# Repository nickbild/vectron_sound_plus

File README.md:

# Vectron Sound Plus

Vectron Sound Plus uses the General Instrument AY-3-8910 sound generator to produce 8-bit retro audio.

## How It Works

The simple design exposes the AY-3-8910's data bus and control pins so that an external system can control it.  The required crystal oscillator and audio output circuitry are also included so that any speaker can be connected via a TRS cable through the onboard jack.

This is the circuit design:

## Media

Here, the Vectron Sound Plus is being controlled by the [Vectron 65 Plus computer](https://github.com/nickbild/vectron_65_plus):

You can download an [MP3 here](https://github.com/nickbild/vectron_sound_plus/blob/main/media/vectron_65_audio.mp3?raw=true) of a tune I made with it.

Vectron Sound Plus can also be controlled via a Raspberry Pi using [my Python library](https://github.com/nickbild/ay-3-8910).

## Bill of Materials

- 1 x General Instrument AY-3-8910 sound generator
- 1 x 2 MHz crystal oscillator
- 1 x 220 uF electrolytic capacitor
- 1 x 47 uF electrolytic capacitor
- 1 x 1K resistor
- 2 x 0.1 uF ceramic capacitors
- 1 x TRS jack connector
- 1 x PCB ([Kicad design files](https://github.com/nickbild/vectron_sound_plus/tree/main/vectron_sound_kicad))

## About the Author

[Nick A. Bild, MS](https://nickbild79.firebaseapp.com/#!/)

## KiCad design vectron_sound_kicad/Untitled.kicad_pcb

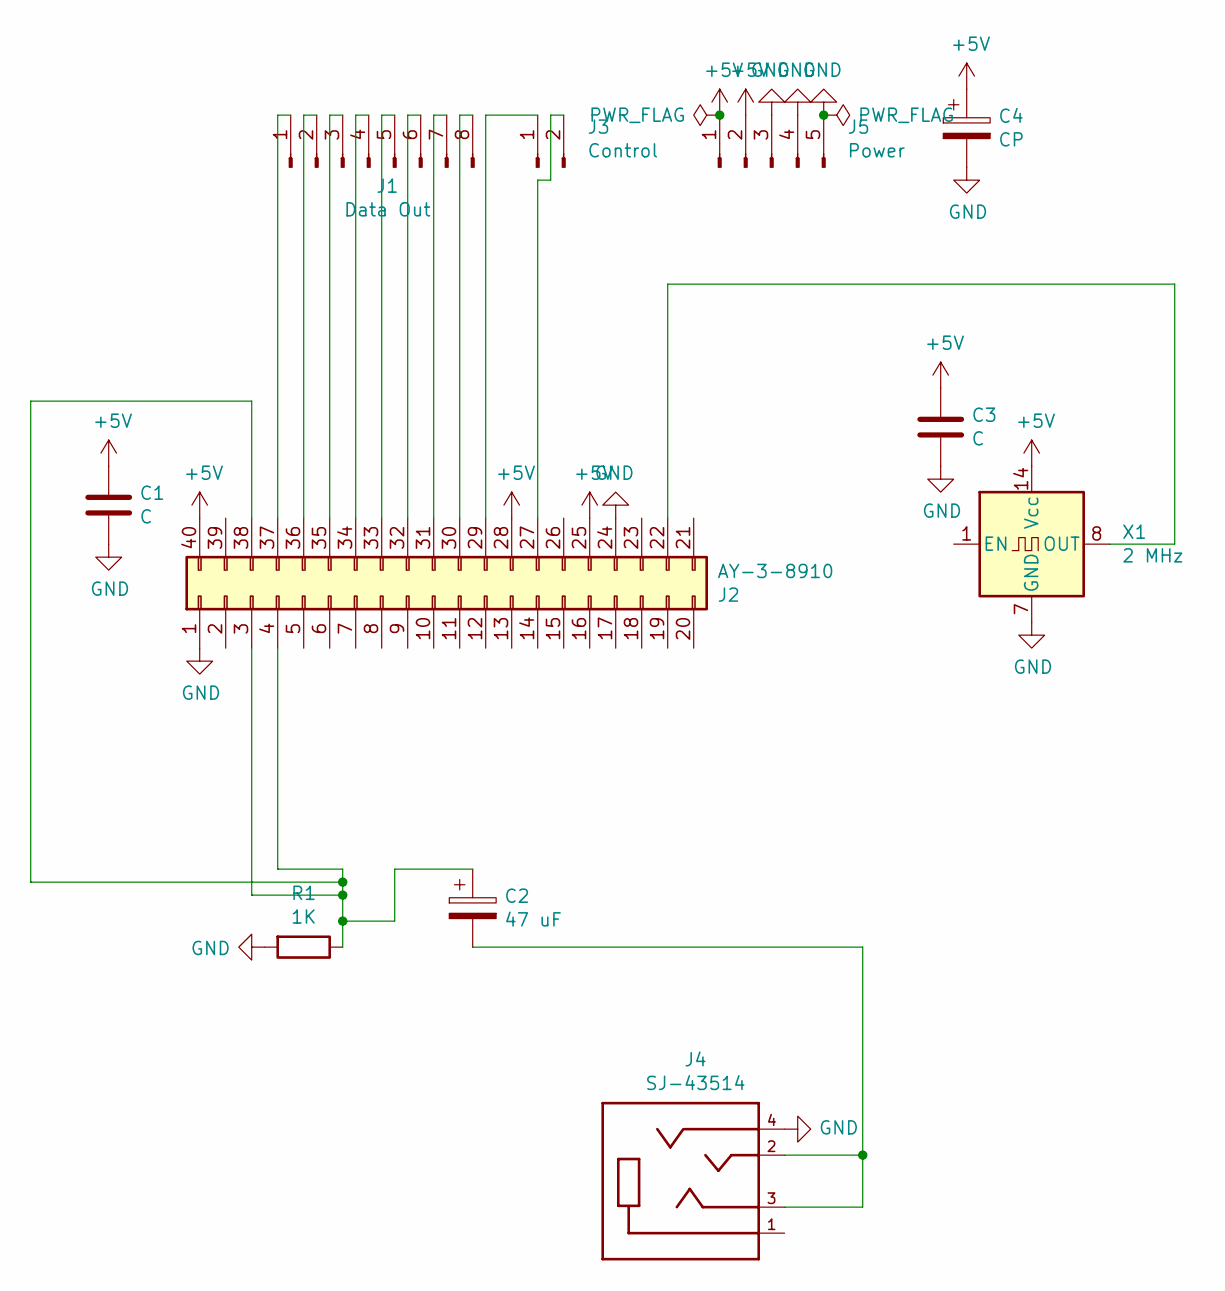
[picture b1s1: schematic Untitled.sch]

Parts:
C1, C3: C; C_Disc_D3.0mm_W2.0mm_P2.50mm
C2: 47 uF; CP_Radial_D4.0mm_P2.00mm
C4: CP; CP_Radial_D5.0mm_P2.50mm
J1: Data Out; PinHeader_1x08_P2.54mm_Vertical
J2: AY-3-8910; DIP-40_W15.24mm
J3: Control; PinHeader_1x02_P2.54mm_Vertical
J4: SJ-43514; CUI_SJ-43514; PART_REV 1.04
J5: Power; PinHeader_1x05_P2.54mm_Vertical
R1: 1K; R_Axial_DIN0204_L3.6mm_D1.6mm_P5.08mm_Horizontal
X1: 2 MHz; Oscillator_DIP-14

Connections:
+5V: C1.1, C3.1, C4.1, J2.25, J2.28, J2.40, J5.1, J5.2, X1.14 (Vcc)
GND: C1.2, C3.2, C4.2, J2.1, J2.24, J4.4, J5.3, J5.4, J5.5, R1.2, X1.7 (GND)
unnamed: C2.1, J2.3, J2.4, J2.38, R1.1
unnamed: C2.2, J4.2, J4.3
unnamed: J1.1, J2.37
unnamed: J1.2, J2.36
unnamed: J1.3, J2.35
unnamed: J1.4, J2.34
unnamed: J1.5, J2.33
unnamed: J1.6, J2.32
unnamed: J1.7, J2.31
unnamed: J1.8, J2.30
unnamed: J2.22, X1.8 (OUT)
unnamed: J2.27, J3.2
unnamed: J2.29, J3.1

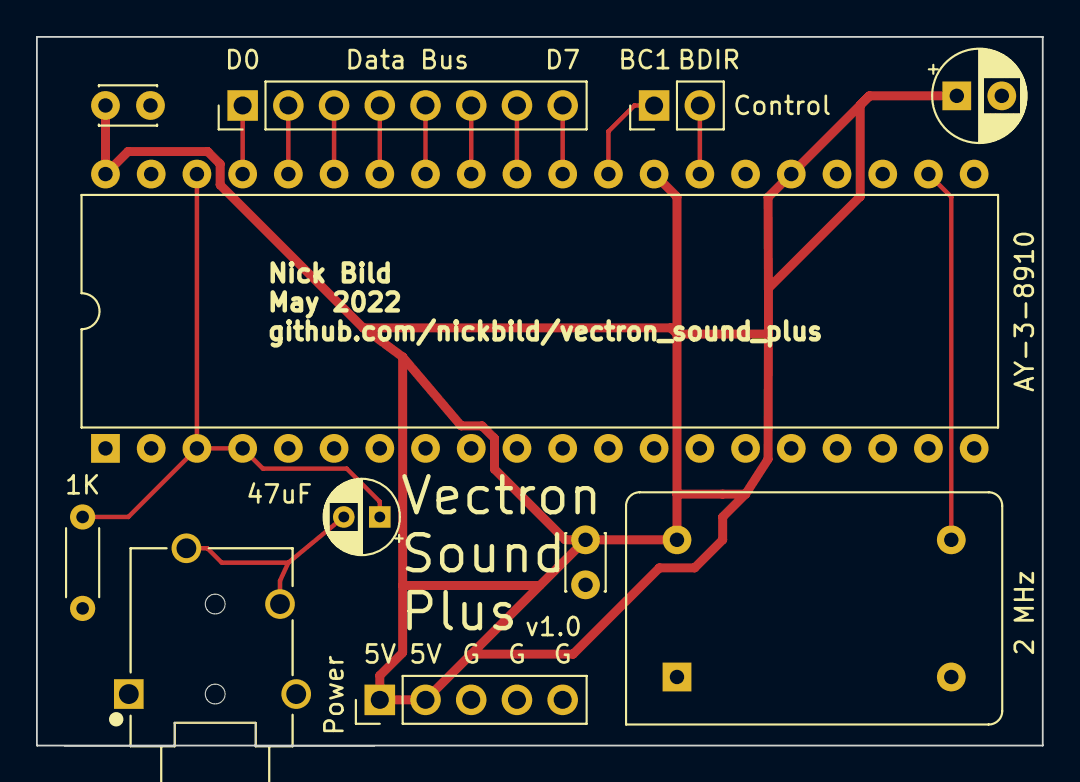
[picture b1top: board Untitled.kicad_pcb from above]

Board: 2 copper layers, 55.9 x 39.4 mm, 11 parts (0 on the bottom side), 15 nets.

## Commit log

2022-05-24 Add KiCad design files.
2022-06-25 Add audio sample.
2022-06-25 RPi POC.
2022-06-25 Update documentation.
